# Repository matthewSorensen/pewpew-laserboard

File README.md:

# PewPew LaserBoard

## What Is It?

LaserBoard is an open source controller for fiber laser marking systems, based around a Teensy 4.1 MCU board. LaserBoard
provides a USB interface compatible with most low-cost fiber laser sources and XY-100-speaking galvanometer scanners, and
supports 4 axes of step/direction motion control. LaserBoard is released under the terms of CERN-OHL-S; see LICENSE.txt,
or [cern_ohl_s_v2.txt](https://ohwr.org/cern_ohl_s_v2.txt) for the full text.

## Q&A

### Why?

At the component level, laser marking hardware is remarkably cheap and high quality, and easy to interface with. Sadly, laser
marker control boards aren't! Generally, they're bundled with a license for low-quality, proprietary software,
greatly inflating the price - a control board with 4 auxiliary axes (eg. JCZ DLC2-M4) cost about as much as a quality
laser source and scanner ($2000!).

Advanced features such as high-precision lens calibration, field stitching, active z-axes control etc. are also very
difficult to implement, as the commercial controllers behave like a black-box and speak an undocumented host/controller
protocol. Some reverse-engineered 3rd party software exists, such as [LightBurn](https://lightburnsoftware.com/) (commercial,
user-friendly high-quality GUI) or [Balor](https://www.bryce.pw/engraver.html) (open-source python interface library),
but controller support is limited.

### Lasers Are Dangerous! Is This Safe?

Lasers can be very dangerous! Unenclosed 10+ watt invisible lasers with peak powers in the low 10s of kW are
absolutely not safe, and a quick scan of YouTokstagram "laser influencer" content will show many poorly educated people
doing very dangerous things with them. Laser safety regulation and enforcement hasn't caught up to the ease with
which anyone can import a turnkey class-4 laser capable of instablindess.

Lasers are also very useful and all of the risks associated with them may be mitigated with proper engineering and
procedural controls. It is essential to fully understand these risks BEFORE purchasing a laser, and if you already
have one, before modifying it or further using it.

If you're in a context with a laser safety officer, talk with them. Laser safety officers are your friends, even
if they seem scary at first.

### What Software Do I Need?

LaserBoard is designed for use with [pewpew-laser](https://github.com/matthewSorensen/pewpew-laser). If that link
appears to be a 404, it's because I'm ambivalent about running an open-source project and haven't figured out the
liability issues related to releasing a complete system. Additionally, there's no GUI or even a standard toolpath
generation script - although there might be some [Rhinoceros](https://www.rhino3d.com/) plugins in the works.

### What Hardware Do I Need?

The following table provides an estimate for a minimal laser marking system with a small Q-switched laser
source, a 50x50 working envelope, a mid-market galvo scanner, and a manually-focused z axis.

|Component         |Example Manufacturer and PN|Budgetary Price        |
|------------------|--------------------------|-----------------------|
|Control Board PCB | LaserBoard-Rev5          |$5-50                  |
|Control Board Components     | Mouser | $90 |
|30W Laser Source | Raycus - RFL-P30QS | $1000 |
|Galvo Scanner | Sino-Galvo SG7110 | $400 |
|F-theta Lens | HY-SL-1064-50-63 | $70 |
|Beam Path | "Fiber Laser Beam Path" | $70 |
|Stand | "Laser Fiber Lift Table" | $120 |
|350W 24V Power Supply | Meanwell LRS-350-24 | $35 |
|2x 15V 2A Power Supplies | CUI VGS-35C-15 | $28 |

Coincidentally, this comes to around $1850 - around $900 cheaper than a plug-and-play commercial system with
roughly the same grade of component. There does seem to be a large amount of price flexibility on laser sources
from certain AliBaba vendors, to the extent that some JPT MOPA sources may be available for around 50% of list price.
However, importing laser sources can pose significant customs issues. Note that this does not include key safety
equipment, such as an enclosure, properly rated laser safety glasses, or an adequate ventilation system; not does
it include wires, terminal blocks, etc.

## Revision History

### Rev 5a

Revision 5a is a minor revision, primarily fixing screwups in Revision 5. The major changes are as follows:

* Pulldown resistors were added to laser output pins, as turn-on behaviour was undefined.

* Board footprint expanded to keep both DB connector faces in-plane and space
was added between the connectors to accommodate cable's overmolded plastic.

* C15 was switched from an SMD part to a PTH part to simplify soldering.

* The pull-up/pull-down selection jumpers for inputs actually work with the
debouncing network and don't require bodge wires.

* The ethernet status LED is routed to the correct pins on the magjack.

### Rev 5

Revision 5 is, in some ways, a simplification, and breaks pin mapping backwards compatibility. The major
changes are as follows:

* The MCU board is changed from a Teensy 4.0 to a Teensy 4.1, in order to access more GPIO and remove a messy SMD
 header on the bottom of the board.

* Proper power supply input - small fiber lasers generally run on 24VDC supplies, and galvo scanners required -15/15V
 supplies, so there's always a readily available DC rail to generate a 5V rail for the teensy. The input protection
 circuit and switcher is essentially the same as published [here](https://blog.thea.codes/starfish-a-control-board-with-the-rp2040/),
 although it omits reverse polarity protection and uses a small polyfuse due to much lower current demands. The board
 may also be powered off a USB connection by shifting the location of a jumper.

* The Q-switch protection circuitry is removed, as the current firmware seems to be robust enough to trust with not
 generating Q-switch clock glitches, and the broader frequency range required for MOPA sources renders it useless.

* Previously, the standard 8-bit parallel laser power interface used a shift register to reduce the GPIO requirement - now,
  8 GPIO pins directly control the power. Supporting MOPA serial data stream with the shift register would have
  required bit-banging a serial stream to bit bang a serial stream - although this was technically feasible, the code
  complexity would have been annoying, and the switch to a parallel interface only required four extra pins.

* Four limit pins are properly debounced with a low-pass filter and Schmitt-trigger and have (jumper) configurable
  pull-up/down resistors and indicator LEDs.

* The teensy 4.1 ethernet phy is broken out to an on-board magjack.

### Rev 4

Rev 4 fixed a bodge wire needed for rev 3 and slightly modified the laser pinout to
support JPT long-pulse sources, although that is as of yet untested.

### Rev 3

Rev 2 incorporated the following changes:

* Support for a two-axis galvanometer scanner communicating over XY-100, requiring
  adding a DB-15 interface and four differential line drivers.
* Motor interfaces were moved to 4 polarized 4 pin molex 0,1" headers.

Rev 3 is still in active use.

### Rev 1 and 2

Revision one was ordered 2021/5/4, and had the following features:

* One DB-25 interface for a q-switched fiber laser, with a one-shot timer
  used to protect the laser from abnormal q-switch pulse trains, a shift
  register for the power control interface, and a hardware interlock to
  require a good q-switch clock signal, a good e-stop signal, and software
  enabling of the laser.
* Four step/direction interfaces, level-shifted to 5V and broken out on a
  single 0.1" header.
* A schmitt-triggered and debounced e-stop input.
* 9 GPIO broken out on a 0.1" header, with no level-shifting or signal conditioning.

Revision one was used with a stepper-driven micrometer stage to get a proof-of-concept
working for some surface-patterning applications, and was quickly replaced with rev 2 -
seemingly a mostly cosmetic modification .

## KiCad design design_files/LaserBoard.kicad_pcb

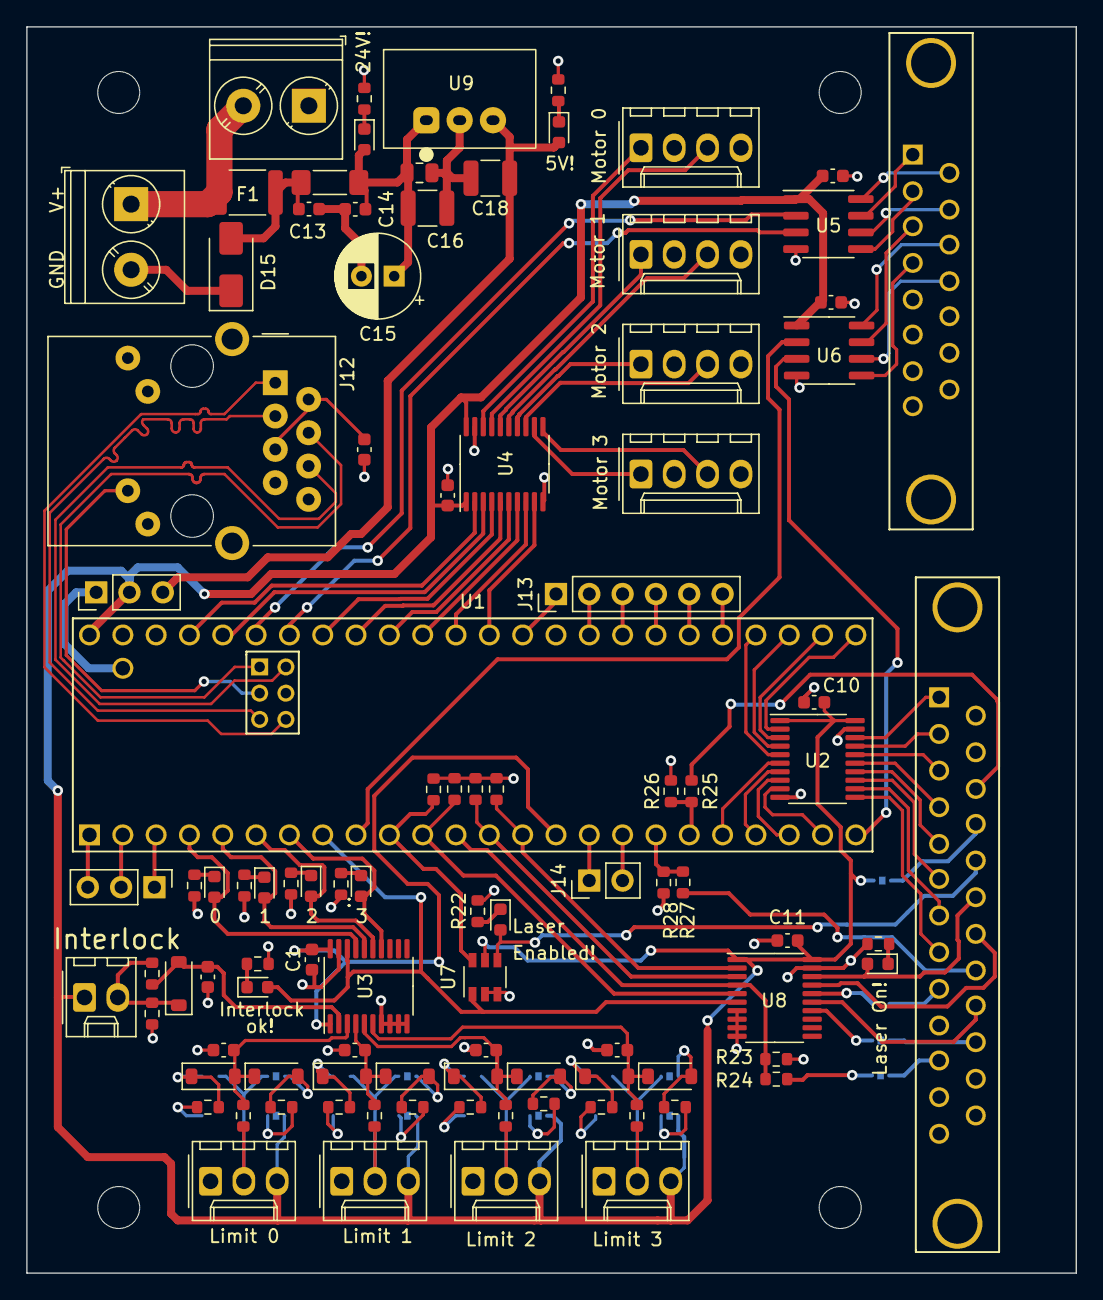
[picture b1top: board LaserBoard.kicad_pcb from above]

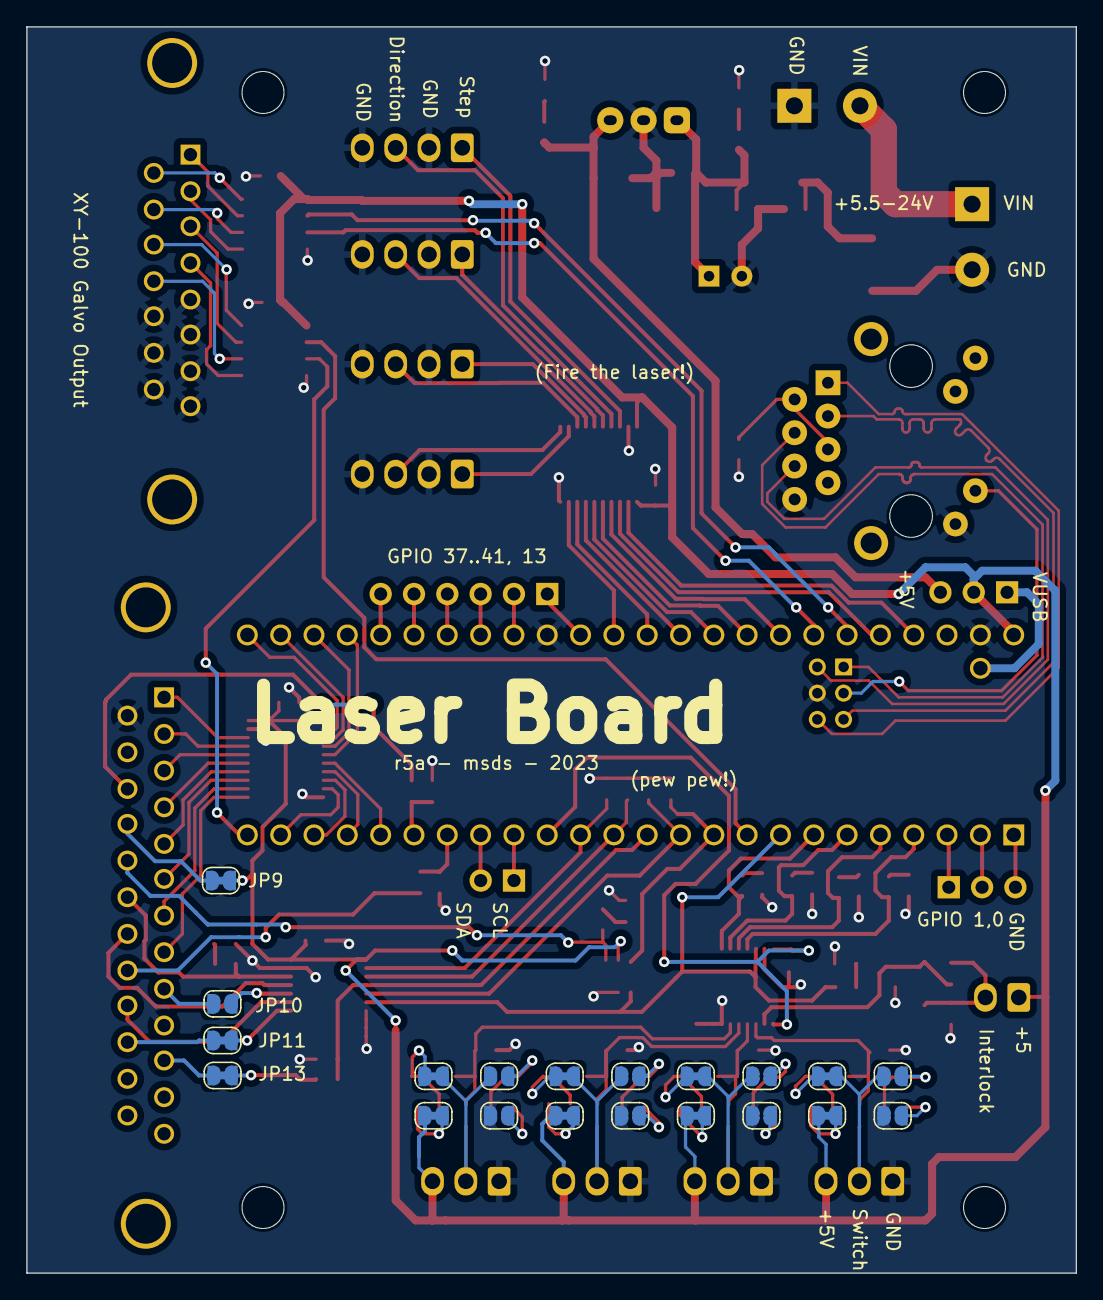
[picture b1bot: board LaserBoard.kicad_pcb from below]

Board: 2 copper layers, 80.0 x 95.0 mm, 123 parts (20 on the bottom side), 129 nets.

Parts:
C1, C7, C8, C9, C10, C11: 0.1uF, 25V; C_0603_1608Metric
C2, C3, C4, C5, C6: 1uF; C_0603_1608Metric
C12, C13, C14: 0.1uF, 50V; C_0603_1608Metric
C15: 100uF, 35V; CP_Radial_D6.3mm_P2.50mm
C16, C18: 10uF 35V; C_1210_3225Metric
C17: 4.7uF 35V; C_0805_2012Metric
D1, D2, D3, D4, D5, D6, D7, D8, D10: 1N4148W-7-F; D_SOD-123
D9: RED LED; LED_0603_1608Metric
D11, D12, D13, D14, D16, D17, D18: GREEN LED; LED_0603_1608Metric
D15: SMAJ28CA; D_SMA
D19: BLUE LED; LED_0603_1608Metric
F1: 300mA PPTC; R_1812_4532Metric
FB1: 60R @ 100MHz, 6A; L_1806_4516Metric_Pad1.45x1.90mm_HandSolder
H1, H2, H3, H4: MountingHole; MountingHole_3.2mm_M3_DIN965
J1, J2, J3, J4: Type KK 1x03 Socket; Molex_KK-254_AE-6410-03A_1x03_P2.54mm_Vertical
J5: Type KK 1x02 Socket; Molex_KK-254_AE-6410-02A_1x02_P2.54mm_Vertical
J6, J7, J8, J9: Type KK 1x04 Socket; Molex_KK-254_AE-6410-04A_1x04_P2.54mm_Vertical
J10: DA15_Receptacle; DB15FD
J11: DB25_Receptacle; DB25FD
J12: RJ45_Amphenol_RJMG1BD3B8K1ANR
J13: Conn_01x06; PinHeader_1x06_P2.54mm_Vertical
J14: Conn_01x02_Pin; PinHeader_1x02_P2.54mm_Vertical
J15: Conn_01x03; PinHeader_1x03_P2.54mm_Vertical
J17, J18: Screw_Terminal_01x02; TerminalBlock_Phoenix_PT-1,5-2-5.0-H_1x02_P5.00mm_Horizontal
JP1, JP2, JP4, JP6, JP8, JP10, JP16, JP18, JP20: Jumper 2 Position, Open; SolderJumper-2_P1.3mm_Open_RoundedPad1.0x1.5mm
JP3, JP5, JP7, JP14, JP15, JP17, JP19, JP21: Jumper_2_Bridged; SolderJumper-2_P1.3mm_Bridged_RoundedPad1.0x1.5mm
JP9, JP11, JP13: Jumper 2 Position, Closed; SolderJumper-2_P1.3mm_Bridged_RoundedPad1.0x1.5mm
JP12: Jumper 3 Position, Open; PinHeader_1x03_P2.54mm_Vertical
R1, R2, R3, R4, R5, R6, R7, R8, R9, R10, R11, R12, R14, R15, R24, R25, R27, R30, R31, R32, R33: R10K; R_0603_1608Metric
R13, R16, R17, R18, R19, R20, R21, R22, R23, R26, R28, R29: R20K; R_0603_1608Metric
U1: Teensy4.1; Teensy41
U2, U3, U4, U8: 74HC245; TSSOP-20_4.4x6.5mm_P0.65mm
U5, U6: UA9638CDR; SOIC-8_3.9x4.9mm_P1.27mm
U7: 74LVC1G3208; TSOP-6_1.65x3.05mm_P0.95mm
U9: VX7805-500; Converter_DCDC_CUI_VX78-500_THT

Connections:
5V_SUPPLY: C18.1, D16.2 (A), JP12.3 (B), U9.3 (Vout)
+3.3V: C1.2, U1.15 (3V3), U3.1 (A->B), U3.20 (VCC)
+5V: C7.2, C8.1, C9.1, C10.1, C11.2, J1.3, J2.3, J3.3, J4.3, J5.1, JP3.1 (A), JP5.1 (A), JP7.1 (A), JP9.1 (A), JP12.2 (C), JP14.1 (A), U1.48 (VIN), U2.1 (A->B), U2.20 (VCC), U4.1 (A->B), U4.20 (VCC), U5.1 (VCC), U6.1 (VCC), U7.5 (VCC), U8.1 (A->B), U8.20 (VCC)
+24V: C14.1, C15.1, C16.1, C17.2, D17.2 (A), FB1.1, U9.1 (Vin)
/R+: J12.R4 (RD+), U1.60 (R+)
/R-: J12.R6 (RD-), U1.65 (R-)
/T+: J12.R1 (TD+), U1.63 (T+)
/T-: J12.R3 (TD-), U1.62 (T-)
ALARM_0_5V: J11.11, JP13.2 (B)
ALARM_0/POWER_LATCH: R23.1, R24.2, U1.12 (10_CS_MQSR), U8.4 (A2)
ALARM_1: R25.2, R26.1, U1.19 (27_A13_SCK1)
ALARM_1_5V: J11.16, R25.1
ALARM_2: R27.2, R28.1, U1.18 (26_A12_MOSI1)
ALARM_2_5V: J11.21, R27.1
DIR0: U1.44 (22_A8_CTX1), U4.3 (A1)
DIR1: U1.40 (18_A4_SDA), U4.5 (A3)
DIR2: U1.38 (16_A2_RX4_SCL1), U4.7 (A5)
DIR3: U1.36 (14_A0_TX3_SPDIF_OUT), U4.9 (A7)
ENABLE: R30.1, U1.10 (8_TX2_IN1), U7.6
GALVO_CLOCK: U1.43 (21_A7_RX5_BCLK1), U5.2 (IN)
GALVO_D1: U1.9 (7_RX2_OUT1A), U6.2 (IN)
GALVO_D2: U1.24 (32_OUT1B), U6.3 (IN)
GALVO_SYNC: U1.42 (20_A6_TX5_LRCLK1), U5.3 (IN)
GND: C1.1, C2.2, C3.2, C4.2, C5.2, C6.2, C7.1, C8.2, C9.2, C10.2, C11.1, C12.1, C13.2, C14.2, C15.2, C16.2, C17.1, C18.2, D15.1 (A1), J1.1, J2.1, J3.1, J4.1, J6.2, J6.4, J7.2, J7.4, J8.2, J8.4, J9.2, J9.4, J10.5, J10.6, J10.7, J10.8, J10.13, J10.14, J10.15, J11.10, J11.14, J12.L1 (LEDY_A), J12.R8 (GND), J17.1, J18.2, JP2.2 (B), JP4.2 (B), JP6.2 (B), JP8.2 (B), R13.2, R14.1, R16.2, R17.2, R18.2, R19.2, R20.1, R21.1, R22.2, R23.2, R26.2, R28.2, R29.2, R30.2, R31.1, R32.1, R33.1, U1.34 (GND), U1.47 (GND), U1.64 (GND), U2.10 (GND), U2.19 (CE), U3.7 (A5), U3.8 (A6), U3.9 (A7), U3.10 (GND), U3.19 (CE), U4.10 (GND), U4.19 (CE), U5.4 (GND), U6.4 (GND), U7.2 (GND), U7.3, U8.7 (A5), U8.8 (A6), U8.9 (A7), U8.10 (GND), U8.19 (CE), U9.2 (GND)
GUIDE_LASER: R31.2, U1.11 (9_OUT1C), U8.5 (A3)
INTERLOCK: D9.2 (A), U1.8 (6_OUT1D), U3.18 (B0), U7.1, U8.6 (A4)
LIMIT0: D14.2 (A), U1.4 (2_OUT2), U3.17 (B1)
LIMIT1: D13.2 (A), U1.5 (3_LRCLK2), U3.16 (B2)
LIMIT2: D12.2 (A), U1.6 (4_BCLK2), U3.15 (B3)
LIMIT3: D11.2 (A), U1.7 (5_IN2), U3.14 (B4)
MODULATE: R33.2, U1.14 (12_MISO_MQSL), U8.2 (A0)
unnamed: D1.2 (A), JP15.1 (A), R2.2
unnamed: C2.1, D1.1 (K), D2.2 (A), R1.2, U3.3 (A1)
unnamed: D2.1 (K), JP1.1 (A), R3.2
unnamed: D3.2 (A), JP17.1 (A), R4.2
unnamed: C3.1, D3.1 (K), D4.2 (A), R6.2, U3.4 (A2)
unnamed: D4.1 (K), JP16.1 (A), R5.2
unnamed: D5.2 (A), JP19.1 (A), R7.2
unnamed: C4.1, D5.1 (K), D6.2 (A), R11.2, U3.5 (A3)
unnamed: D6.1 (K), JP18.1 (A), R8.2
unnamed: D7.2 (A), JP21.1 (A), R9.2
unnamed: C5.1, D7.1 (K), D8.2 (A), R12.2, U3.6 (A4)
unnamed: D8.1 (K), JP20.1 (A), R10.2
unnamed: D9.1 (K), R13.1
unnamed: C6.1, D10.2 (A), R15.2, U3.2 (A0)
unnamed: D10.1 (K), J5.2, R14.2, R15.1
unnamed: D11.1 (K), R16.1
unnamed: D12.1 (K), R17.1
unnamed: D13.1 (K), R18.1
unnamed: D14.1 (K), R19.1
unnamed: D16.1 (K), R20.2
unnamed: D17.1 (K), R21.2
unnamed: D18.1 (K), R22.1
unnamed: D19.2 (A), J11.19, U8.18 (B0)
unnamed: D19.1 (K), R29.1
unnamed: J1.2, JP1.2 (B), JP15.2 (B), R1.1
unnamed: J2.2, JP16.2 (B), JP17.2 (B), R6.1
unnamed: J3.2, JP18.2 (B), JP19.2 (B), R11.1
unnamed: J4.2, JP20.2 (B), JP21.2 (B), R12.1
unnamed: J6.1, U4.18 (B0)
unnamed: J6.3, U4.17 (B1)
unnamed: J7.1, U4.16 (B2)
unnamed: J7.3, U4.15 (B3)
unnamed: J8.1, U4.14 (B4)
unnamed: J8.3, U4.13 (B5)
unnamed: J9.1, U4.12 (B6)
unnamed: J9.3, U4.11 (B7)
unnamed: J10.9, U5.8 (OUTB)
unnamed: J10.10, U5.6 (OUTB)
unnamed: J10.12, U6.6 (OUTB)
unnamed: J10.11 (P111), U6.8 (OUTB)
unnamed: J11.17, JP9.2 (B)
unnamed: J11.20, U8.17 (B1)
unnamed: J11.22, U8.15 (B3)
unnamed: J11.23, JP11.2 (B)
unnamed: J12.L2 (LEDY_K), U1.61 (LED)
unnamed: C12.2, J12.R2 (TCT), J12.R5 (RCT)
unnamed: J13.1, U1.35 (13_SCK_LED)
unnamed: J13.2, U1.33 (41_A17)
unnamed: J13.3, U1.32 (40_A16)
unnamed: J13.4, U1.31 (39_MISO1_OUT1A)
unnamed: J13.5, U1.30 (38_CS1_IN1)
unnamed: J13.6, U1.29 (37_CS)
unnamed: J14.1, U1.16 (24_A10_TX6_SCL2)
unnamed: J14.2, U1.17 (25_A11_RX6_SDA2)
unnamed: J15.1, U1.3 (1_TX1_CTX2_MISO1)
unnamed: J15.2, U1.2 (0_RX1_CRX2_CS1)
unnamed: J15.3, U1.1 (GND)
unnamed: JP2.1 (A), R3.1
unnamed: JP3.2 (B), R4.1
unnamed: JP4.1 (A), R5.1
unnamed: JP5.2 (B), R7.1
unnamed: JP6.1 (A), R8.1
unnamed: JP7.2 (B), R9.1
unnamed: JP8.1 (A), R10.1
unnamed: JP10.1 (A), U8.16 (B2)
unnamed: J11.9, JP10.2 (B)
unnamed: JP11.1 (A), U8.14 (B4)
unnamed: JP12.1 (A), U1.49 (VUSB)
unnamed: JP13.1 (A), R24.1
unnamed: JP14.2 (B), R2.1
unnamed: J11.1, U2.18 (B0)
unnamed: J11.2, U2.17 (B1)
unnamed: J11.3, U2.16 (B2)
unnamed: J11.4, U2.15 (B3)
unnamed: J11.5, U2.14 (B4)
unnamed: J11.6, U2.13 (B5)
unnamed: J11.7, U2.12 (B6)
unnamed: J11.8, U2.11 (B7)
unnamed: J10.1, U5.7 (OUTA)
unnamed: J10.2, U5.5 (OUTA)
unnamed: J10.3, U6.7 (OUTA)
unnamed: J10.4, U6.5 (OUTA)
PWR_0: U1.25 (33_MCLK2), U2.2 (A0)
PWR_1/SER_DATA: U1.26 (34_RX8), U2.3 (A1)
PWR_2/SER_CLOCK: U1.27 (35_TX8), U2.4 (A2)
PWR_3: U1.28 (36_CS), U2.5 (A3)
PWR_4: U1.20 (28_RX7), U2.6 (A4)
PWR_5: U1.21 (29_TX7), U2.7 (A5)
PWR_6: U1.22 (30_CRX3), U2.8 (A6)
PWR_7: U1.23 (31_CTX3), U2.9 (A7)
RAW_24: C13.1, D15.2 (A2), F1.1, FB1.2
SAFE_ENABLE: D18.2 (A), J11.18, U7.4
STEP0: U1.45 (23_A9_CRX1_MCLK1), U4.2 (A0)
STEP1: U1.41 (19_A5_SCL), U4.4 (A2)
STEP2: U1.39 (17_A3_TX4_SDA1), U4.6 (A4)
STEP3: U1.37 (15_A1_RX3_SPDIF_IN), U4.8 (A6)
SYNC: R32.2, U1.13 (11_MOSI_CTX1), U8.3 (A1)
V_INPUT: F1.2, J17.2, J18.1

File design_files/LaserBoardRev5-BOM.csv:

Reference,Value,Mouser Part Number,Manufacturer Part Number,Qty,Notes
"C1, C7-C11","0.1uF, 25V",187-CL05A104KA5NNNC,CL05A104KA5NNNC,6,Generic decoupling cap
C2-C6,1uF,810-CGA3E1X7R1C105AC,CGA3E1X7R1C105AC,5,
C12-C14,"0.1uF, 50V",80-C603C104K5RAC3121,C603C104K5RAC3121,3,
C15,"100uF, 35V",710-865080653016,865080653016,1,
"C16, C18",10uF 35V,187-CL32A106KAULNNE,CL32A106KAULNNE,2,
C17,4.7uF 35V,187-CL21A475KLCLQNC,CL21A475KLCLQNC,1,
"D1-D8, D10",1N4148W-7-F,621-1N4148W-F,1N4148W-F,9,
D9,RED LED,710-150060RS75000,150060RS75000,1,
"D11-D14, D16-D18",GREEN LED,710-150060GS75000,150060GS75000,7,
D15,SMAJ28CA,576-SMAJ28CA,SMAJ28CA,1,
D19,BLUE LED,710-150060BS75000,150060BS75000,1,
F1,300mA PPTC,650-MINISMDC030F-2,MINISMDC030F-2,1,
FB1,"60R @ 100MHz, 6A",81-BLM41P600S,BLM41PG600SN1L,1,
J1-J4,Type KK 1x03 Socket,710-61900311121,61900311121,4,
J5,Type KK 1x02 Socket,710-61900211121,61900211121,1,
J6-J9,Type KK 1x04 Socket,710-61900411121,61900411121,4,
J10,DA15_Receptacle,710-618015231321,618015231321,1,
J11,DB25_Receptacle,710-618025231121,618025231121,1,
J12,RJ45_Amphenol_RJMG1BD3B8K1ANR,710-618015231321,618015231321,1,
"J17, J18",Screw_Terminal_01x02,490-TB002-500-02BE,TB002-500-02BE,2,
"R1-R12, R14, R15, R24, R25, R27",R10K,603-RC0603JR-0710KL,RC0603JR-0710KL,17,
"R13, R16-R23, R26, R28, R29",R20K,603-RC0603JR-0720KL,RC0603JR-0720KL,12,
U1,Teensy4.1,474-DEV-16771,TEENSY41,1,Don't purchase from Mouser - export control paperwork is slow
"U2-U4, U8",74HC245,771-74AHC245PW-Q100J,74AHC245PW-Q100J,4,
"U5, U6",UA9638CDR,595-UA9638CDR,UA9638CDR,2,
U7,74LVC1G3208,595-SN74LC1G3208DBVR,SN74LC1G3208DBVR,1,
U9,VX7805-500,490-VX7805-500,VX7805-500,1,
Teensy Ethernet Header,2x3 2mm Pitch Header,571-2MM-HBD03VT02HTB,2MM-HBD03VT02HTB,1,"Alternately, purchase 1x ETHERNET_KIT from PJRC, and skip J12"
"JP12, J13,J14,J15, Teensy Headers","1x24 0.1"" Breakaway Headers",538-22-28-4244,22-28-4244,3,
Jumper for power,"0.1"" Jumper",710-60900213421,60900213421,1,
,,,,,
External Connectors,External Connectors,,,,
Reference,Value,Mouser Part Number,Manufacturer Part Number,Qty,Notes
J1-J4,Type KK 1x03 Terminal Housing,710-61900311621,61900311621,4,
J5,Type KK 1x02 Terminal Housing,710-61900211621,61900211621,1,
J6-J9,Type KK 1x04 Terminal Housing,710-61900411621,61900411621,4,
,Female Crimp Contact,710-61900113722DEC,61900113722DEC,33,

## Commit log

2023-05-31 Compile a bit of the history of the previous revs, and think about what we want to change
2023-06-25 mostly update documentation for laser board r5
2023-06-25 Rev5 design files; still need to generate a proper BOM and assembly docs
2023-06-25 write a snarky readme
2023-06-25 write a snarky readme for real
2023-06-25 add license info
2023-06-25 And that's why we write documentation - two small errors on the pcb
2023-07-01 BOM, readme update
2023-10-08 Rev 5a
2023-10-08 rev5a is a minor enough change that I'm comfortable removing that
2023-10-27 Add new images, purge an old schematic sheet, and update the package of a component to match the datasheet.
